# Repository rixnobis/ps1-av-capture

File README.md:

# ps1-av-capture

A capture board for the PlayStation's analog RGB and line audio. A TI TVP7002
digitises the 15 kHz RGB from the multi-out, a Cypress FX3 carries the pixels to the
host over USB 3 as a UVC camera, and a TI PCM2903C presents the audio as a USB
sound card. This first revision is one channel; the plan is three on one board
behind a hub.

Work in progress: nothing here has been built. Part availability is in
[docs/parts.md](docs/parts.md).

The video front end follows the OSSC (github.com/marqs85/ossc), which uses the
same digitiser on the same signals. The FX3 side follows Cypress application note
AN75779.

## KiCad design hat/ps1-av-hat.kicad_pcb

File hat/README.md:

# PS1 AV capture hat

One-channel PS1 capture hat for the Maker go CH32H417QEU6 dev board. Schematic: `gen_hat_sch.py`
(`tools/`); board: `tools/build_hat_pcb.py` (outline, headers, holes, placement, no routing);
`./build.sh` runs everything (ERC, netlist checks, PCB, DRC, renders in `renders/`).

## Mechanics
- The hat plugs on the dev board through two 3x19 2.54 mm headers (J4 = board U12, J5 = board U13)
  and sits 8-11 mm above it. Geometry comes from the board DXF (`tools/mg_dxf_geometry.json`,
  made by `tools/extract_mg_dxf.py`). Which DXF header is U12 is still unresolved:
  `TOP_IS_U12` in `tools/build_hat_pcb.py` (default True), flip and rebuild.
- The outline keeps 1 mm clear of the dev board's tall parts (barrel jack, screw terminal, RJ45,
  USB-A). The headers run to x = -37.5 (DXF) but the RJ45 starts at -43.1, so the outline is
  notched between two ears; the ears carry the two right-hand mounting holes.
- All four M3 holes of the dev board fall inside the hat outline (H1-H4 match them, 3.2 mm).
  Use standoffs of the header-stack height; the headers are not the only support.
- Placement is for review; nothing is routed. The dev board's tact switches and LEDs near its
  lower-left corner are covered by the hat.

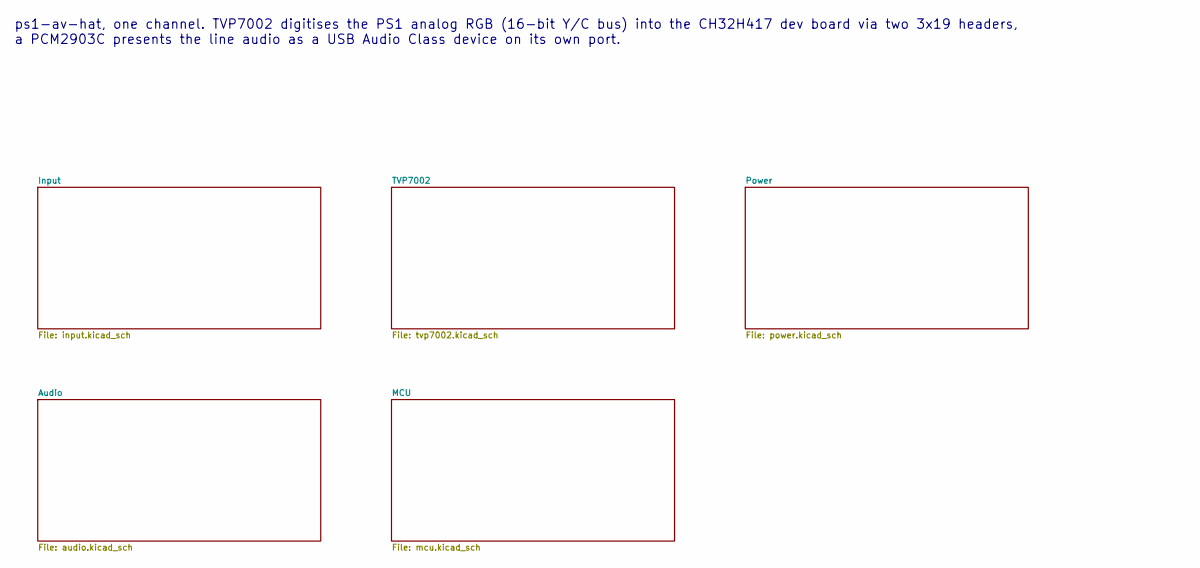
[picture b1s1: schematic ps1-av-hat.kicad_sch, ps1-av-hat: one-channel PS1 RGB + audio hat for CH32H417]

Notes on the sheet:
ps1-av-hat, one channel. TVP7002 digitises the PS1 analog RGB (16-bit Y/C bus) into the CH32H417 dev board via two 3x19 headers, a PCM2903C presents the line audio as a USB Audio Class device on its own port.

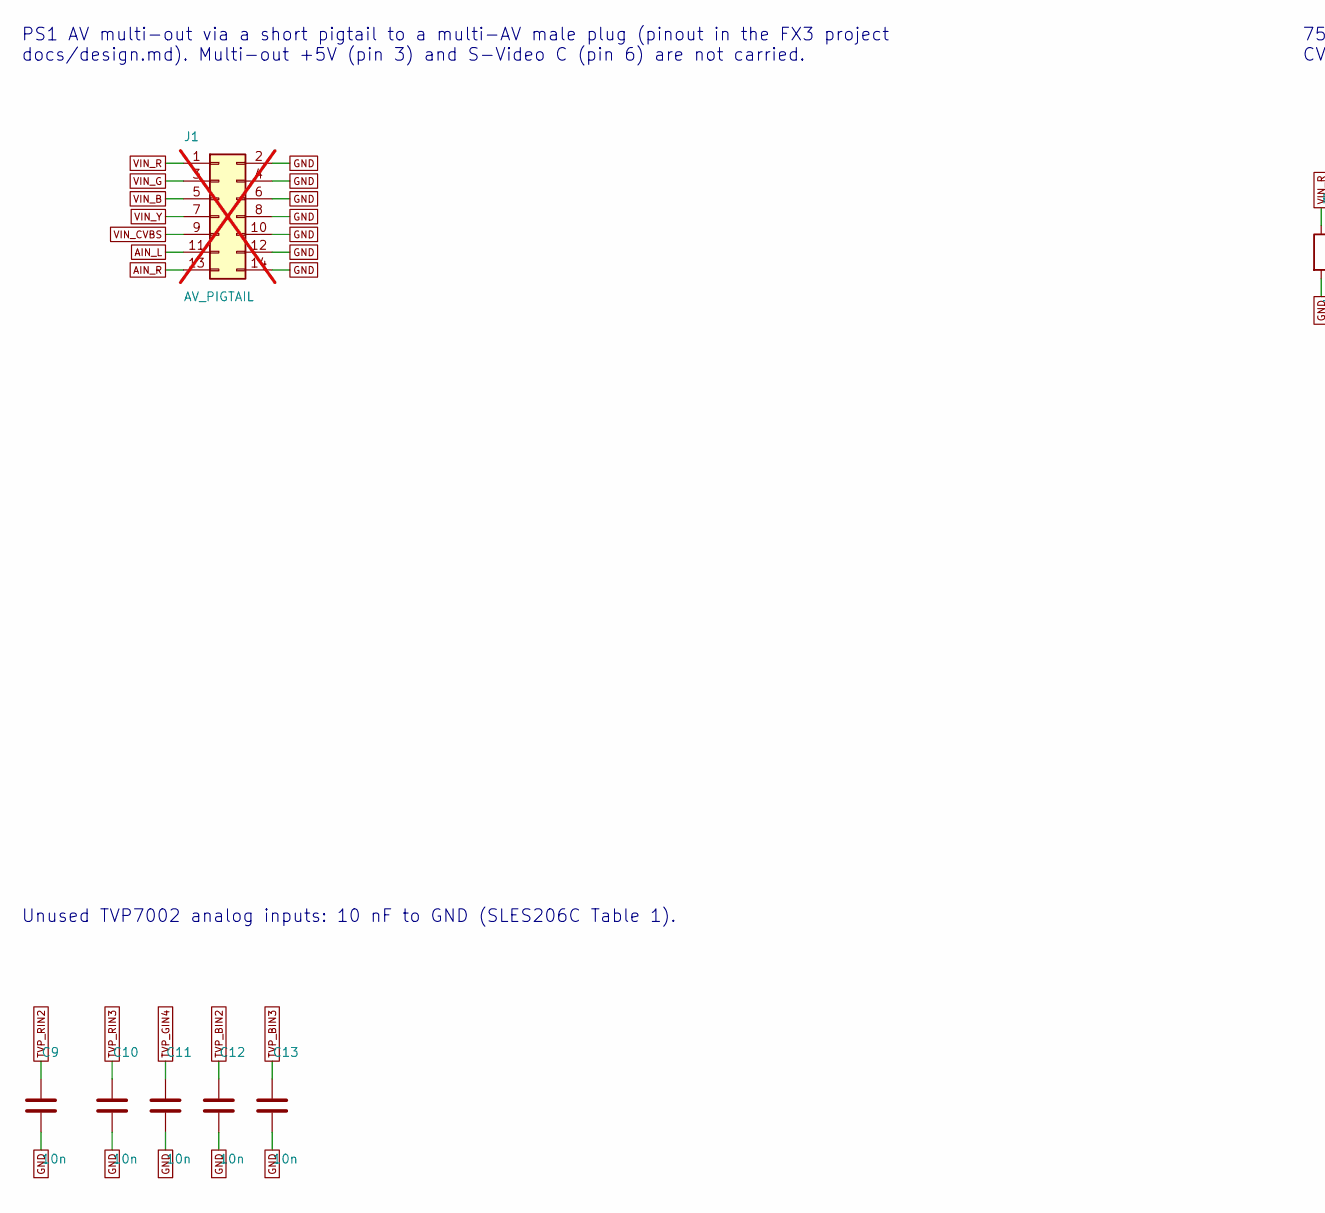
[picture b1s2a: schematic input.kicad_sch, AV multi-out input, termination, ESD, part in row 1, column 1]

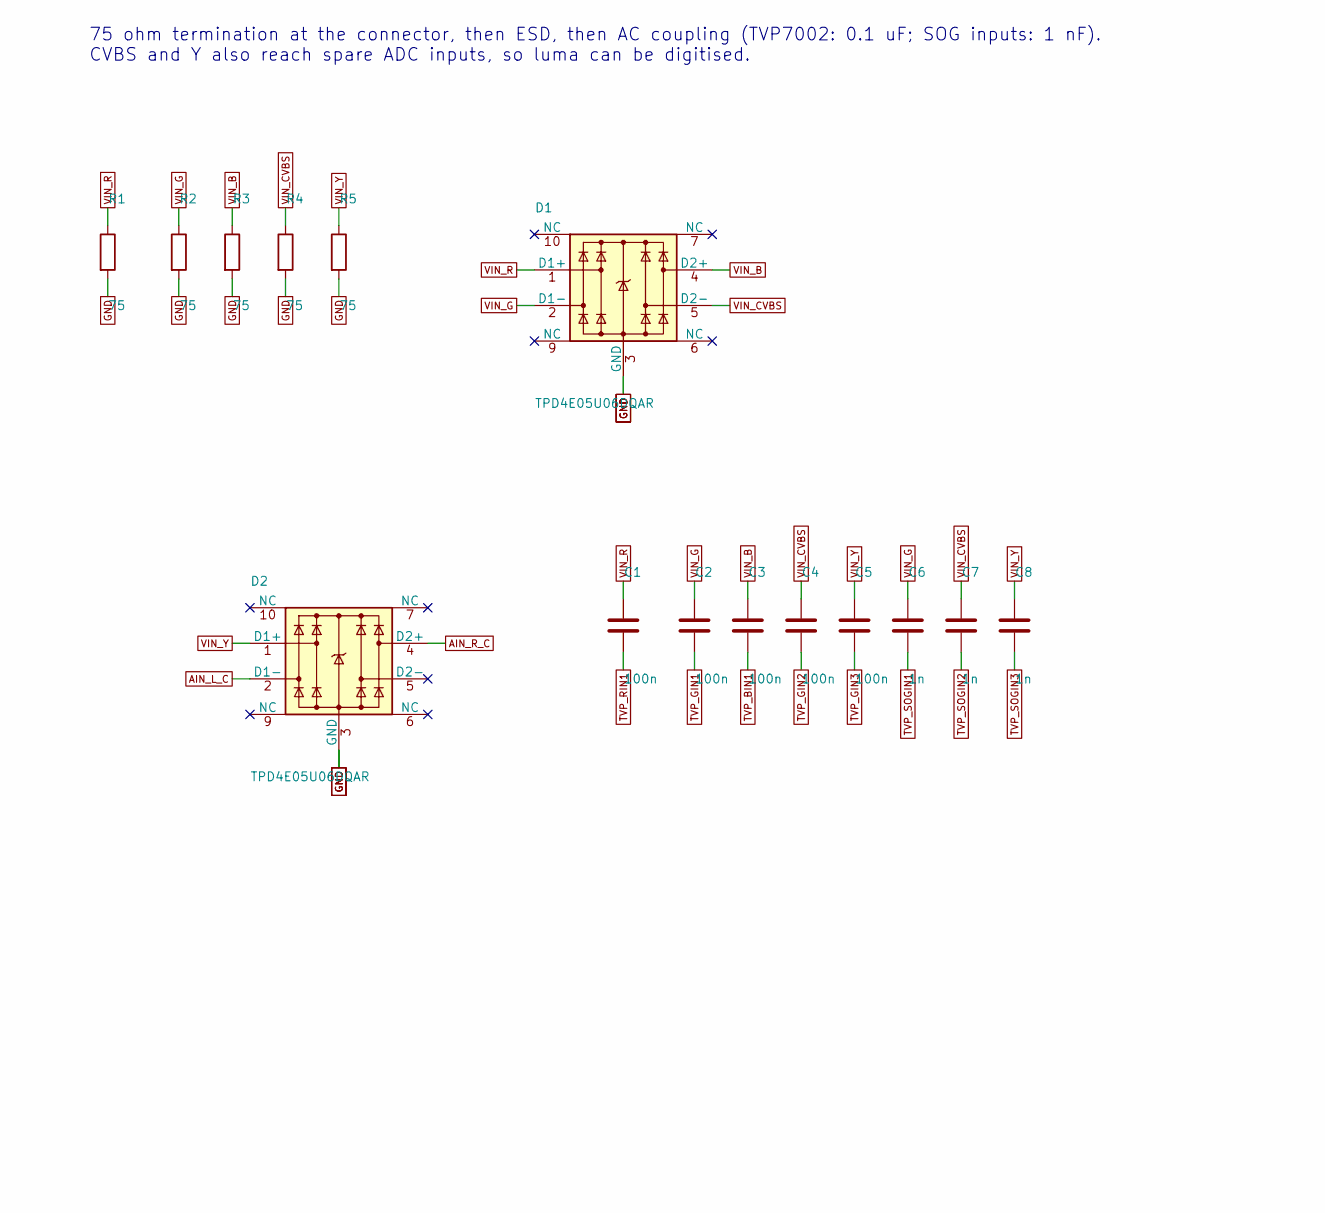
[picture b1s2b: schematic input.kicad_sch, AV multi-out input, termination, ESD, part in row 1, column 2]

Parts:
C1, C2, C3, C4, C5: 100n; C_0402_1005Metric; LCSC C1525
C6, C7, C8: 1n; C_0402_1005Metric; LCSC C1523
C9, C10, C11, C12, C13: 10n; C_0402_1005Metric; LCSC C15195
D1, D2: TPD4E05U06DQAR; USON-10_2.5x1.0mm_P0.5mm; LCSC C138714
J1: AV_PIGTAIL; JST_PHD_B14B-PHDSS_2x07_P2.00mm_Vertical; LCSC C471471; not fitted
R1, R2, R3, R4, R5: 75; R_0402_1005Metric; LCSC C25133

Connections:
AIN_L: J1.11; also elsewhere on the board
AIN_L_C: D2.2 (D1-); also elsewhere on the board
AIN_R: J1.13; also elsewhere on the board
AIN_R_C: D2.4 (D2+); also elsewhere on the board
GND: C9.2, C10.2, C11.2, C12.2, C13.2, D1.3 (GND), D1.8 (GND), D2.3 (GND), D2.8 (GND), J1.2, J1.4, J1.6, J1.8, J1.10, J1.12, J1.14, R1.2, R2.2, R3.2, R4.2, R5.2; also elsewhere on the board
TVP_BIN1: C3.2; also elsewhere on the board
TVP_BIN2: C12.1; also elsewhere on the board
TVP_BIN3: C13.1; also elsewhere on the board
TVP_GIN1: C2.2; also elsewhere on the board
TVP_GIN2: C4.2; also elsewhere on the board
TVP_GIN3: C5.2; also elsewhere on the board
TVP_GIN4: C11.1; also elsewhere on the board
TVP_RIN1: C1.2; also elsewhere on the board
TVP_RIN2: C9.1; also elsewhere on the board
TVP_RIN3: C10.1; also elsewhere on the board
TVP_SOGIN1: C6.2; also elsewhere on the board
TVP_SOGIN2: C7.2; also elsewhere on the board
TVP_SOGIN3: C8.2; also elsewhere on the board
VIN_B: C3.1, D1.4 (D2+), J1.5, R3.1
VIN_CVBS: C4.1, C7.1, D1.5 (D2-), J1.9, R4.1
VIN_G: C2.1, C6.1, D1.2 (D1-), J1.3, R2.1
VIN_R: C1.1, D1.1 (D1+), J1.1, R1.1
VIN_Y: C5.1, C8.1, D2.1 (D1+), J1.7, R5.1

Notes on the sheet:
PS1 AV multi-out via a short pigtail to a multi-AV male plug (pinout in the FX3 project docs/design.md). Multi-out +5V (pin 3) and S-Video C (pin 6) are not carried.
75 ohm termination at the connector, then ESD, then AC coupling (TVP7002: 0.1 uF; SOG inputs: 1 nF). CVBS and Y also reach spare ADC inputs, so luma can be digitised.
Unused TVP7002 analog inputs: 10 nF to GND (SLES206C Table 1).

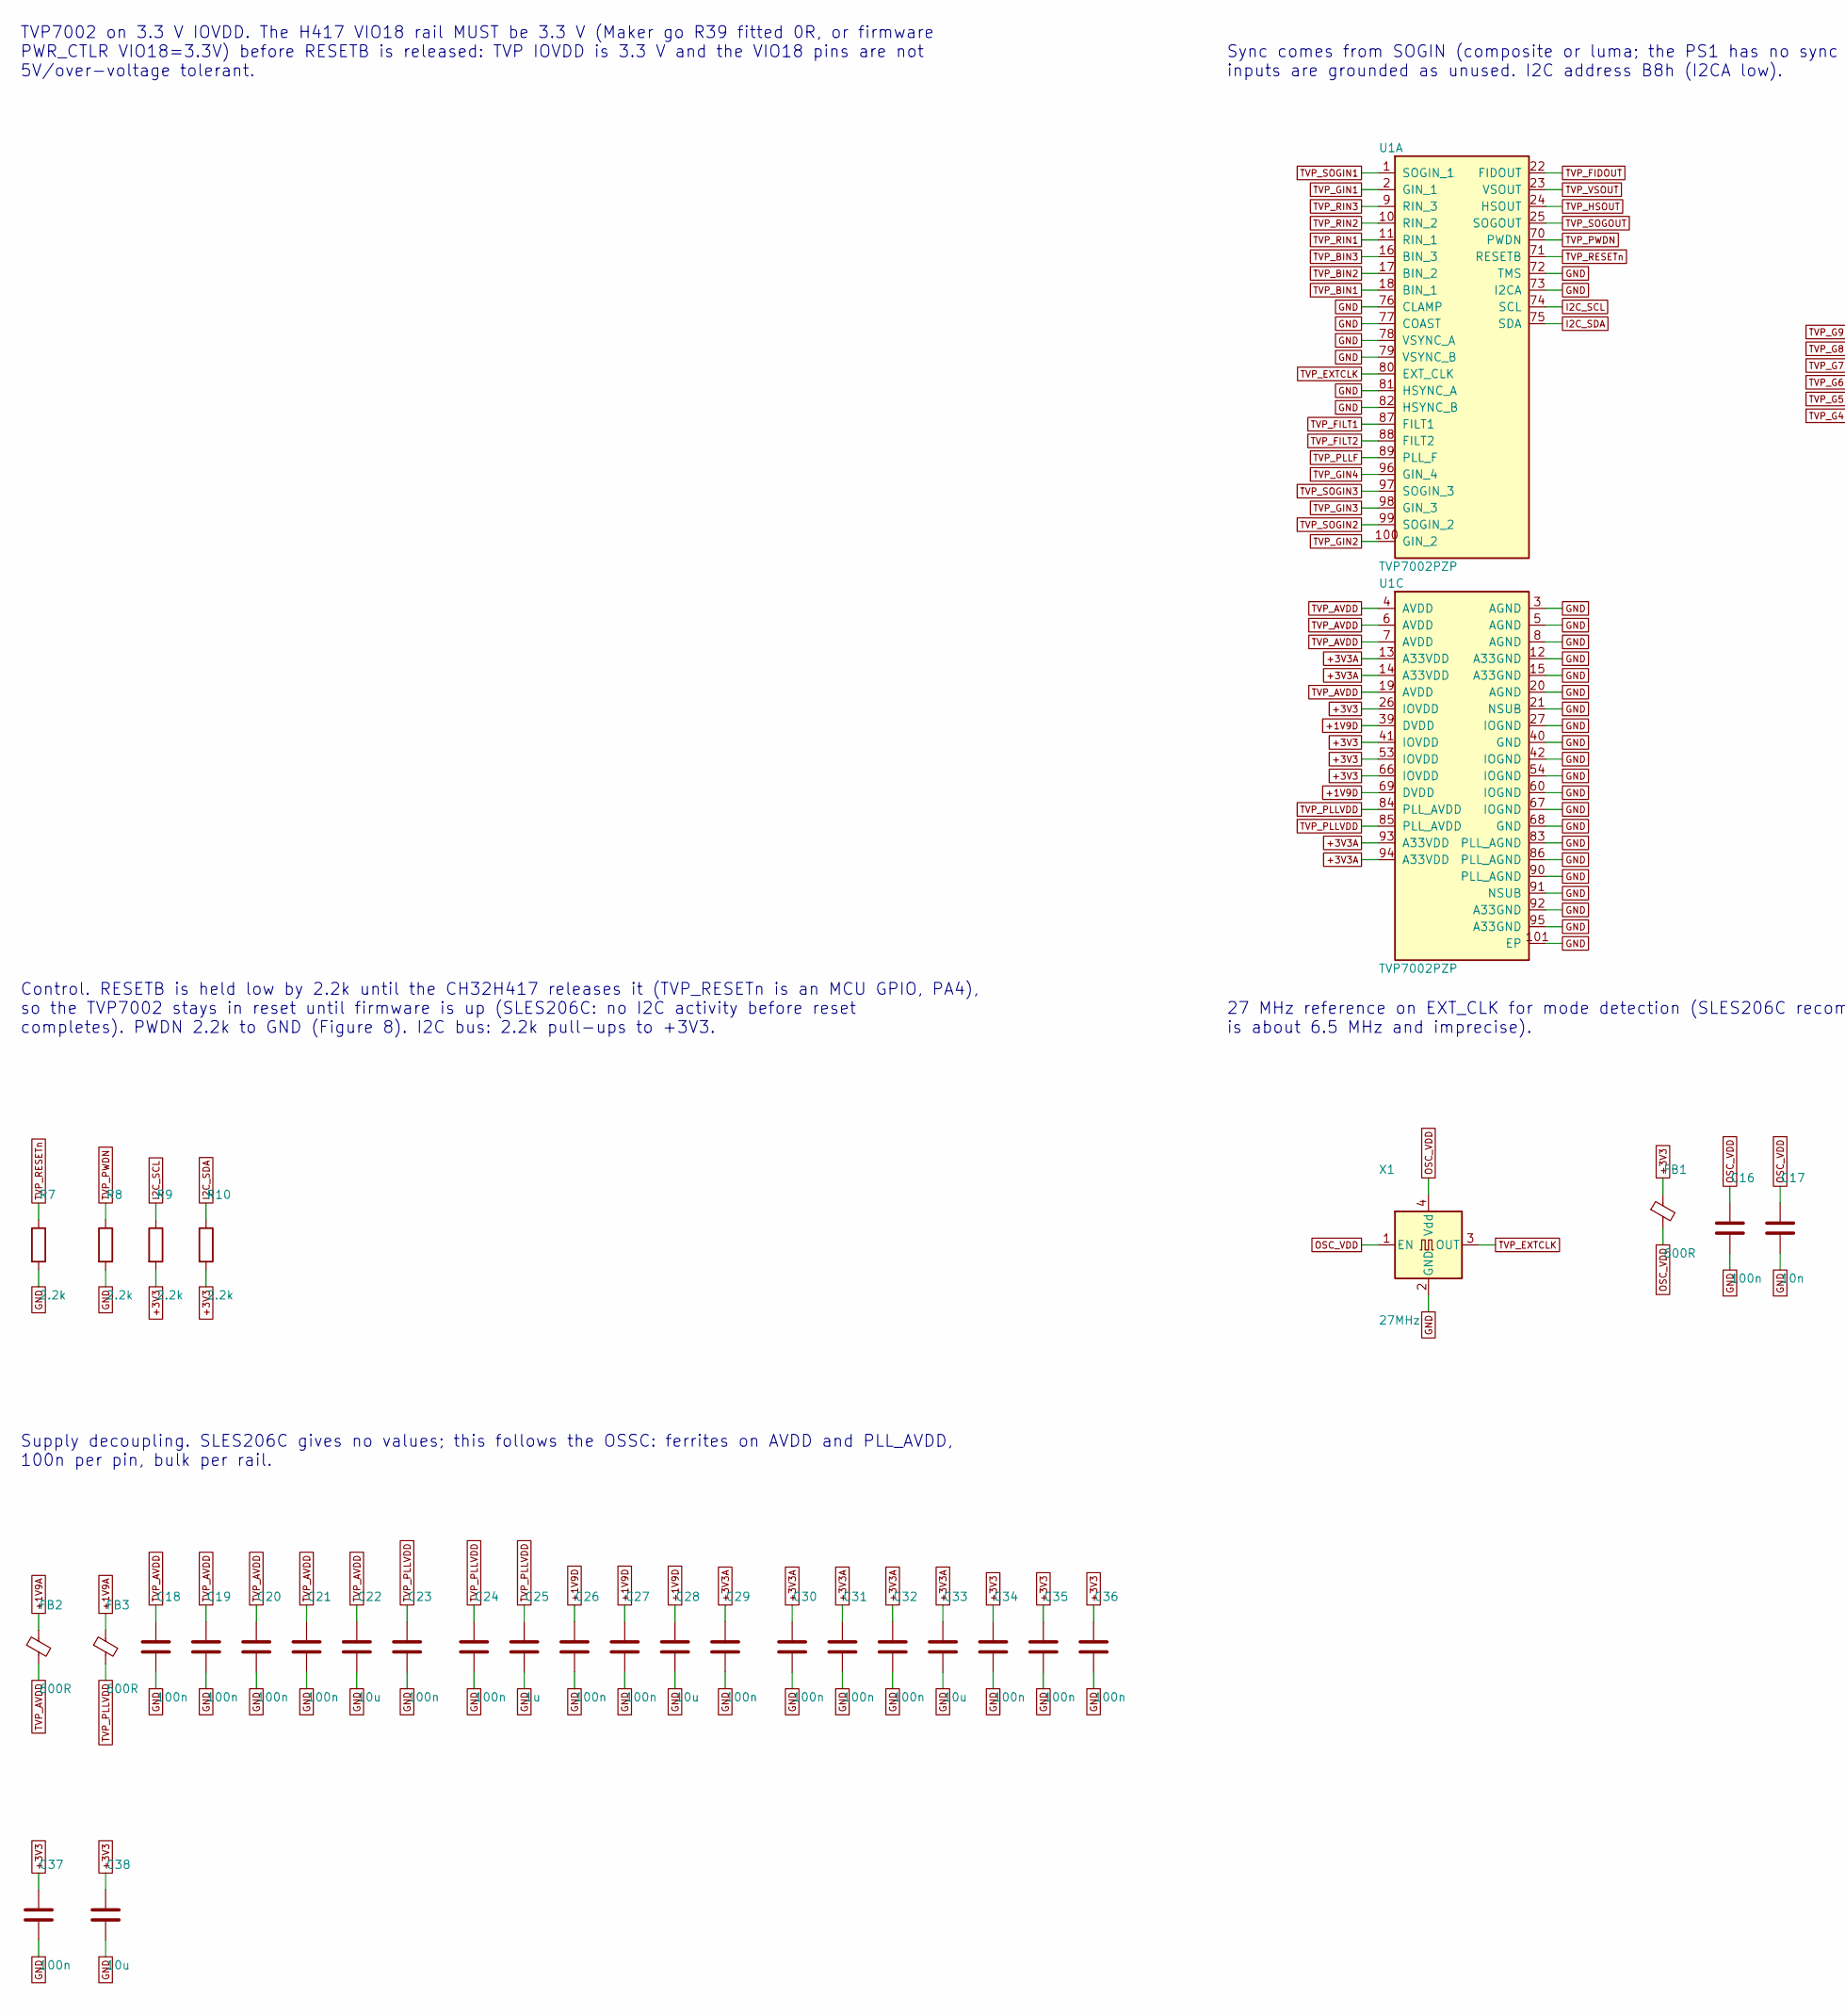
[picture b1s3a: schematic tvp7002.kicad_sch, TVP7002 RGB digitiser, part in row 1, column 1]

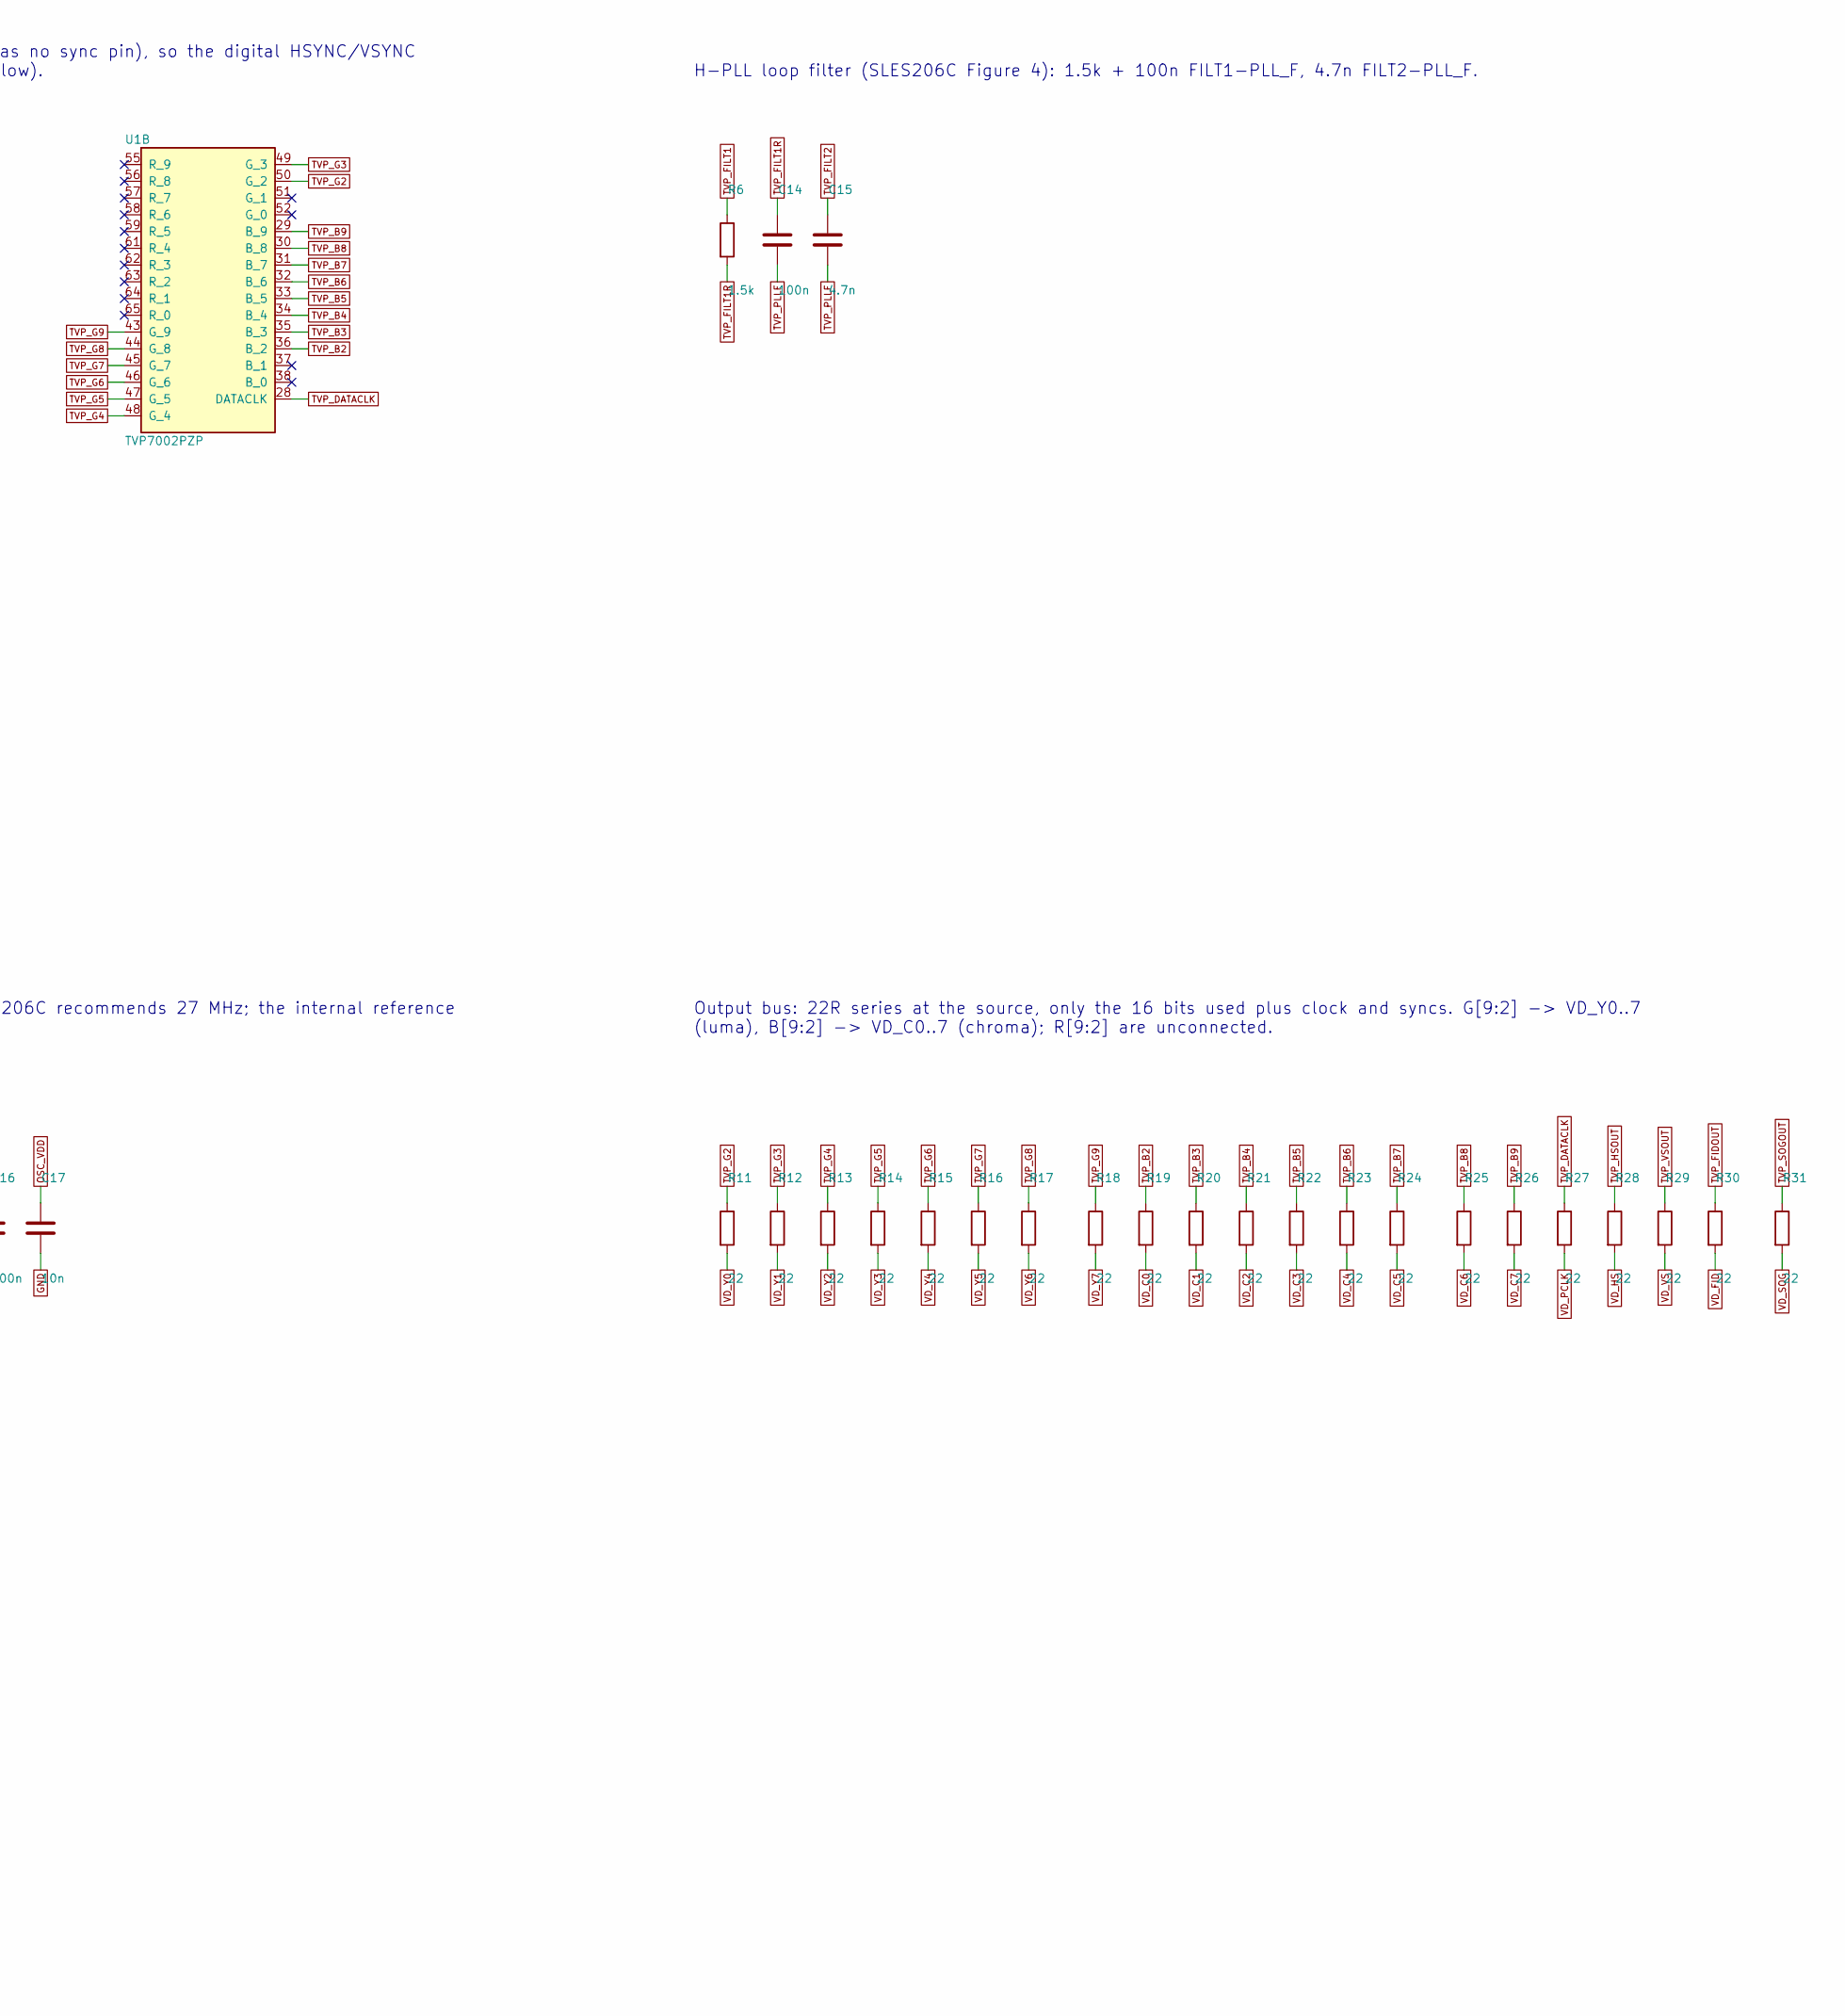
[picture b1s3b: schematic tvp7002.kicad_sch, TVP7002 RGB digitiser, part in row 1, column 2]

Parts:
C14, C16, C18, C19, C20, C21, C23, C24, C26, C27, C29, C30, C31, C32, C34, C35, C36, C37: 100n; C_0402_1005Metric; LCSC C1525
C15: 4.7n; C_0402_1005Metric; LCSC C1538
C17: 10n; C_0402_1005Metric; LCSC C15195
C22, C28, C33, C38: 10u; C_0603_1608Metric; LCSC C19702
C25: 1u; C_0402_1005Metric; LCSC C52923
FB1, FB2, FB3: 600R; L_0603_1608Metric; LCSC C108301
R6: 1.5k; R_0402_1005Metric; LCSC C25867
R7, R8, R9, R10: 2.2k; R_0402_1005Metric; LCSC C25879
R11, R12, R13, R14, R15, R16, R17, R18, R19, R20, R21, R22, R23, R24, R25, R26, R27, R28, R29, R30, R31: 22; R_0402_1005Metric; LCSC C25092
U1: TVP7002PZP; HTQFP-100_L14.0-W14.0-P0.50-LS16.0-BL-EP6.2; LCSC C3824085
X1: 27MHz; Oscillator_SMD_Abracon_ASE-4Pin_3.2x2.5mm; LCSC C725995

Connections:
+1V9A: FB2.1, FB3.1; also elsewhere on the board
+1V9D: C26.1, C27.1, C28.1, U1.39 (DVDD), U1.69 (DVDD); also elsewhere on the board
+3V3: C34.1, C35.1, C36.1, C37.1, C38.1, FB1.1, R9.2, R10.2, U1.26 (IOVDD), U1.41 (IOVDD), U1.53 (IOVDD), U1.66 (IOVDD); also elsewhere on the board
+3V3A: C29.1, C30.1, C31.1, C32.1, C33.1, U1.13 (A33VDD), U1.14 (A33VDD), U1.93 (A33VDD), U1.94 (A33VDD); also elsewhere on the board
GND: C16.2, C17.2, C18.2, C19.2, C20.2, C21.2, C22.2, C23.2, C24.2, C25.2, C26.2, C27.2, C28.2, C29.2, C30.2, C31.2, C32.2, C33.2, C34.2, C35.2, C36.2, C37.2, C38.2, R7.2, R8.2, U1.3 (AGND), U1.5 (AGND), U1.8 (AGND), U1.12 (A33GND), U1.15 (A33GND), U1.20 (AGND), U1.21 (NSUB), U1.27 (IOGND), U1.40 (GND), U1.42 (IOGND), U1.54 (IOGND), U1.60 (IOGND), U1.67 (IOGND), U1.68 (GND), U1.72 (TMS), U1.73 (I2CA), U1.76 (CLAMP), U1.77 (COAST), U1.78 (VSYNC_A), U1.79 (VSYNC_B), U1.81 (HSYNC_A), U1.82 (HSYNC_B), U1.83 (PLL_AGND), U1.86 (PLL_AGND), U1.90 (PLL_AGND), U1.91 (NSUB), U1.92 (A33GND), U1.95 (A33GND), U1.101 (EP), X1.2 (GND); also elsewhere on the board
I2C_SCL: R9.1, U1.74 (SCL); also elsewhere on the board
I2C_SDA: R10.1, U1.75 (SDA); also elsewhere on the board
OSC_VDD: C16.1, C17.1, FB1.2, X1.1 (EN), X1.4 (Vdd)
TVP_AVDD: C18.1, C19.1, C20.1, C21.1, C22.1, FB2.2, U1.4 (AVDD), U1.6 (AVDD), U1.7 (AVDD), U1.19 (AVDD)
TVP_B2: R19.1, U1.36 (B_2)
TVP_B3: R20.1, U1.35 (B_3)
TVP_B4: R21.1, U1.34 (B_4)
TVP_B5: R22.1, U1.33 (B_5)
TVP_B6: R23.1, U1.32 (B_6)
TVP_B7: R24.1, U1.31 (B_7)
TVP_B8: R25.1, U1.30 (B_8)
TVP_B9: R26.1, U1.29 (B_9)
TVP_BIN1: U1.18 (BIN_1); also elsewhere on the board
TVP_BIN2: U1.17 (BIN_2); also elsewhere on the board
TVP_BIN3: U1.16 (BIN_3); also elsewhere on the board
TVP_DATACLK: R27.1, U1.28 (DATACLK)
TVP_EXTCLK: U1.80 (EXT_CLK), X1.3 (OUT)
TVP_FIDOUT: R30.1, U1.22 (FIDOUT)
TVP_FILT1: R6.1, U1.87 (FILT1)
TVP_FILT1R: C14.1, R6.2
TVP_FILT2: C15.1, U1.88 (FILT2)
TVP_G2: R11.1, U1.50 (G_2)
TVP_G3: R12.1, U1.49 (G_3)
TVP_G4: R13.1, U1.48 (G_4)
TVP_G5: R14.1, U1.47 (G_5)
TVP_G6: R15.1, U1.46 (G_6)
TVP_G7: R16.1, U1.45 (G_7)
TVP_G8: R17.1, U1.44 (G_8)
TVP_G9: R18.1, U1.43 (G_9)
TVP_GIN1: U1.2 (GIN_1); also elsewhere on the board
TVP_GIN2: U1.100 (GIN_2); also elsewhere on the board
TVP_GIN3: U1.98 (GIN_3); also elsewhere on the board
TVP_GIN4: U1.96 (GIN_4); also elsewhere on the board
TVP_HSOUT: R28.1, U1.24 (HSOUT)
TVP_PLLF: C14.2, C15.2, U1.89 (PLL_F)
TVP_PLLVDD: C23.1, C24.1, C25.1, FB3.2, U1.84 (PLL_AVDD), U1.85 (PLL_AVDD)
TVP_PWDN: R8.1, U1.70 (PWDN)
TVP_RESETn: R7.1, U1.71 (RESETB); also elsewhere on the board
TVP_RIN1: U1.11 (RIN_1); also elsewhere on the board
TVP_RIN2: U1.10 (RIN_2); also elsewhere on the board
TVP_RIN3: U1.9 (RIN_3); also elsewhere on the board
TVP_SOGIN1: U1.1 (SOGIN_1); also elsewhere on the board
TVP_SOGIN2: U1.99 (SOGIN_2); also elsewhere on the board
TVP_SOGIN3: U1.97 (SOGIN_3); also elsewhere on the board
TVP_SOGOUT: R31.1, U1.25 (SOGOUT)
TVP_VSOUT: R29.1, U1.23 (VSOUT)
VD_C0: R19.2; also elsewhere on the board
VD_C1: R20.2; also elsewhere on the board
VD_C2: R21.2; also elsewhere on the board
VD_C3: R22.2; also elsewhere on the board
VD_C4: R23.2; also elsewhere on the board
VD_C5: R24.2; also elsewhere on the board
VD_C6: R25.2; also elsewhere on the board
VD_C7: R26.2; also elsewhere on the board
VD_FID: R30.2; also elsewhere on the board
VD_HS: R28.2; also elsewhere on the board
VD_PCLK: R27.2; also elsewhere on the board
VD_SOG: R31.2; also elsewhere on the board
VD_VS: R29.2; also elsewhere on the board
VD_Y0: R11.2; also elsewhere on the board
VD_Y1: R12.2; also elsewhere on the board
VD_Y2: R13.2; also elsewhere on the board
VD_Y3: R14.2; also elsewhere on the board
VD_Y4: R15.2; also elsewhere on the board
VD_Y5: R16.2; also elsewhere on the board
VD_Y6: R17.2; also elsewhere on the board
VD_Y7: R18.2; also elsewhere on the board

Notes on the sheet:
TVP7002 on 3.3 V IOVDD. The H417 VIO18 rail MUST be 3.3 V (Maker go R39 fitted 0R, or firmware PWR_CTLR VIO18=3.3V) before RESETB is released: TVP IOVDD is 3.3 V and the VIO18 pins are not 5V/over-voltage tolerant.
Sync comes from SOGIN (composite or luma; the PS1 has no sync pin), so the digital HSYNC/VSYNC inputs are grounded as unused. I2C address B8h (I2CA low).
H-PLL loop filter (SLES206C Figure 4): 1.5k + 100n FILT1-PLL_F, 4.7n FILT2-PLL_F.
Control. RESETB is held low by 2.2k until the CH32H417 releases it (TVP_RESETn is an MCU GPIO, PA4), so the TVP7002 stays in reset until firmware is up (SLES206C: no I2C activity before reset completes). PWDN 2.2k to GND (Figure 8). I2C bus: 2.2k pull-ups to +3V3.
27 MHz reference on EXT_CLK for mode detection (SLES206C recommends 27 MHz; the internal reference is about 6.5 MHz and imprecise).
Output bus: 22R series at the source, only the 16 bits used plus clock and syncs. G[9:2] -> VD_Y0..7 (luma), B[9:2] -> VD_C0..7 (chroma); R[9:2] are unconnected.
Supply decoupling. SLES206C gives no values; this follows the OSSC: ferrites on AVDD and PLL_AVDD, 100n per pin, bulk per rail.

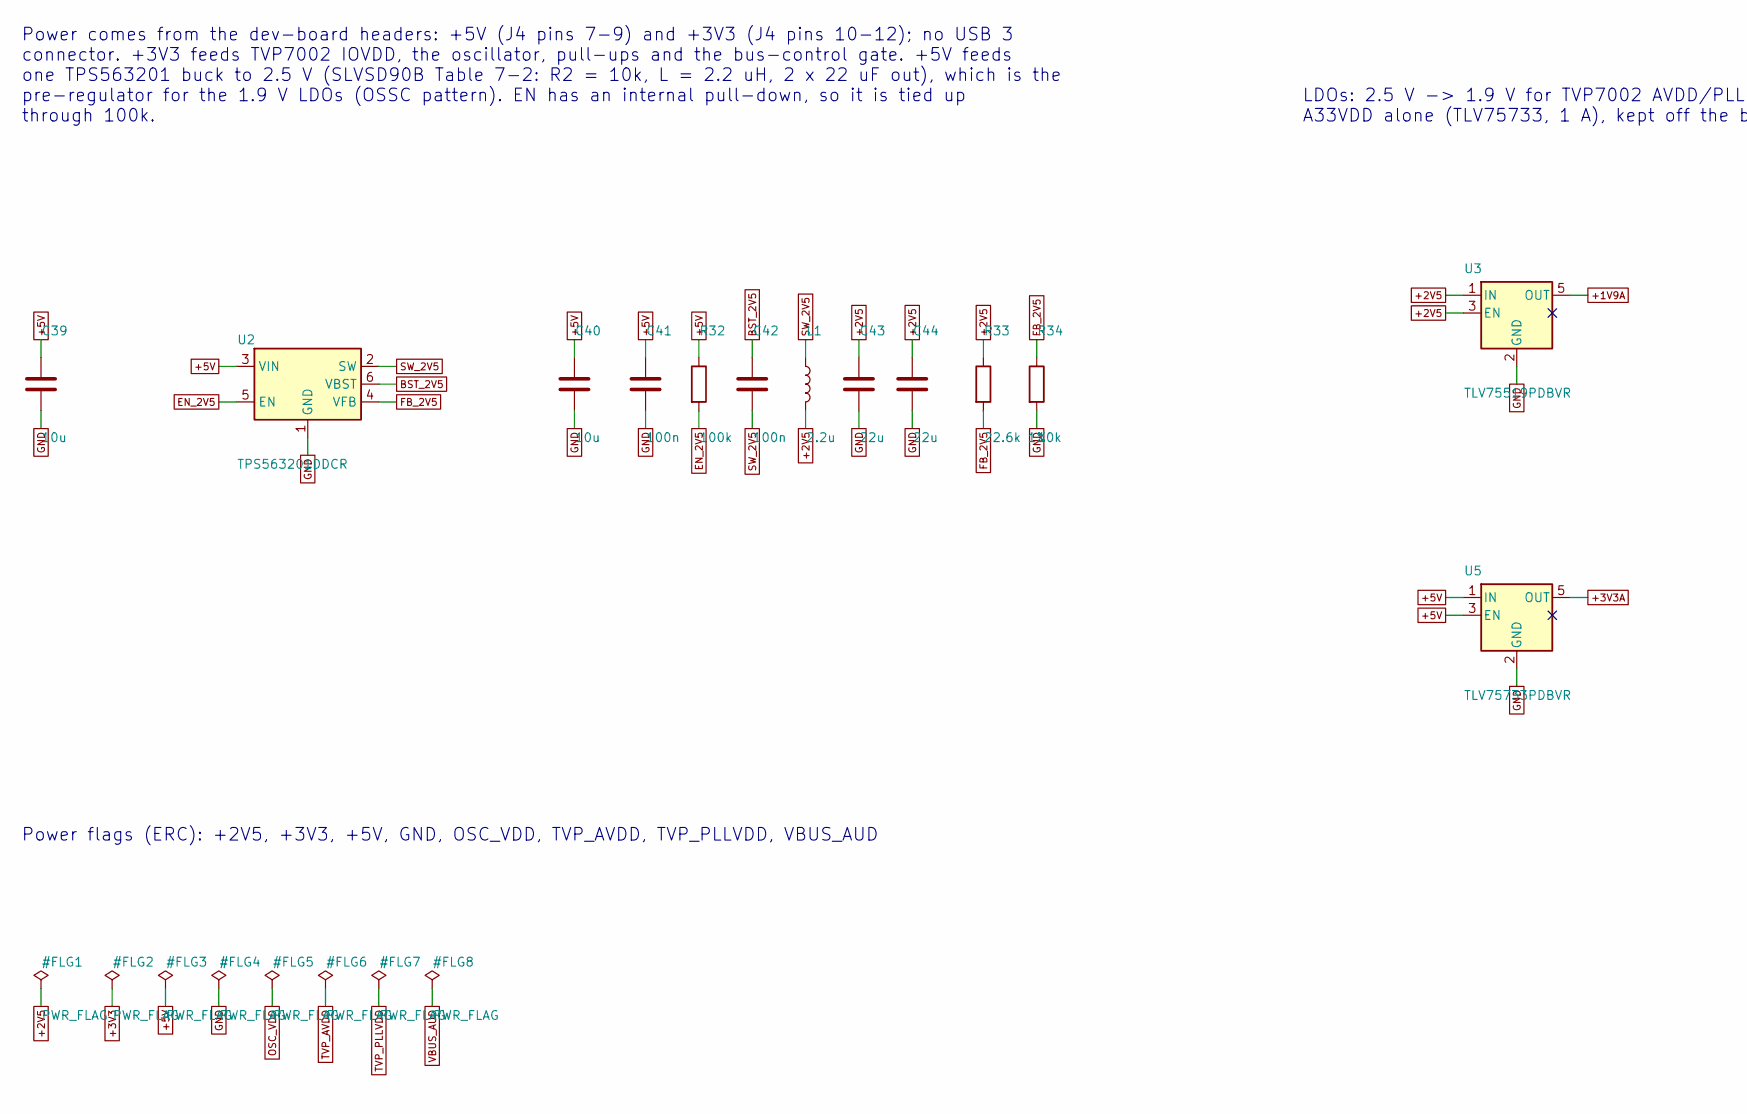
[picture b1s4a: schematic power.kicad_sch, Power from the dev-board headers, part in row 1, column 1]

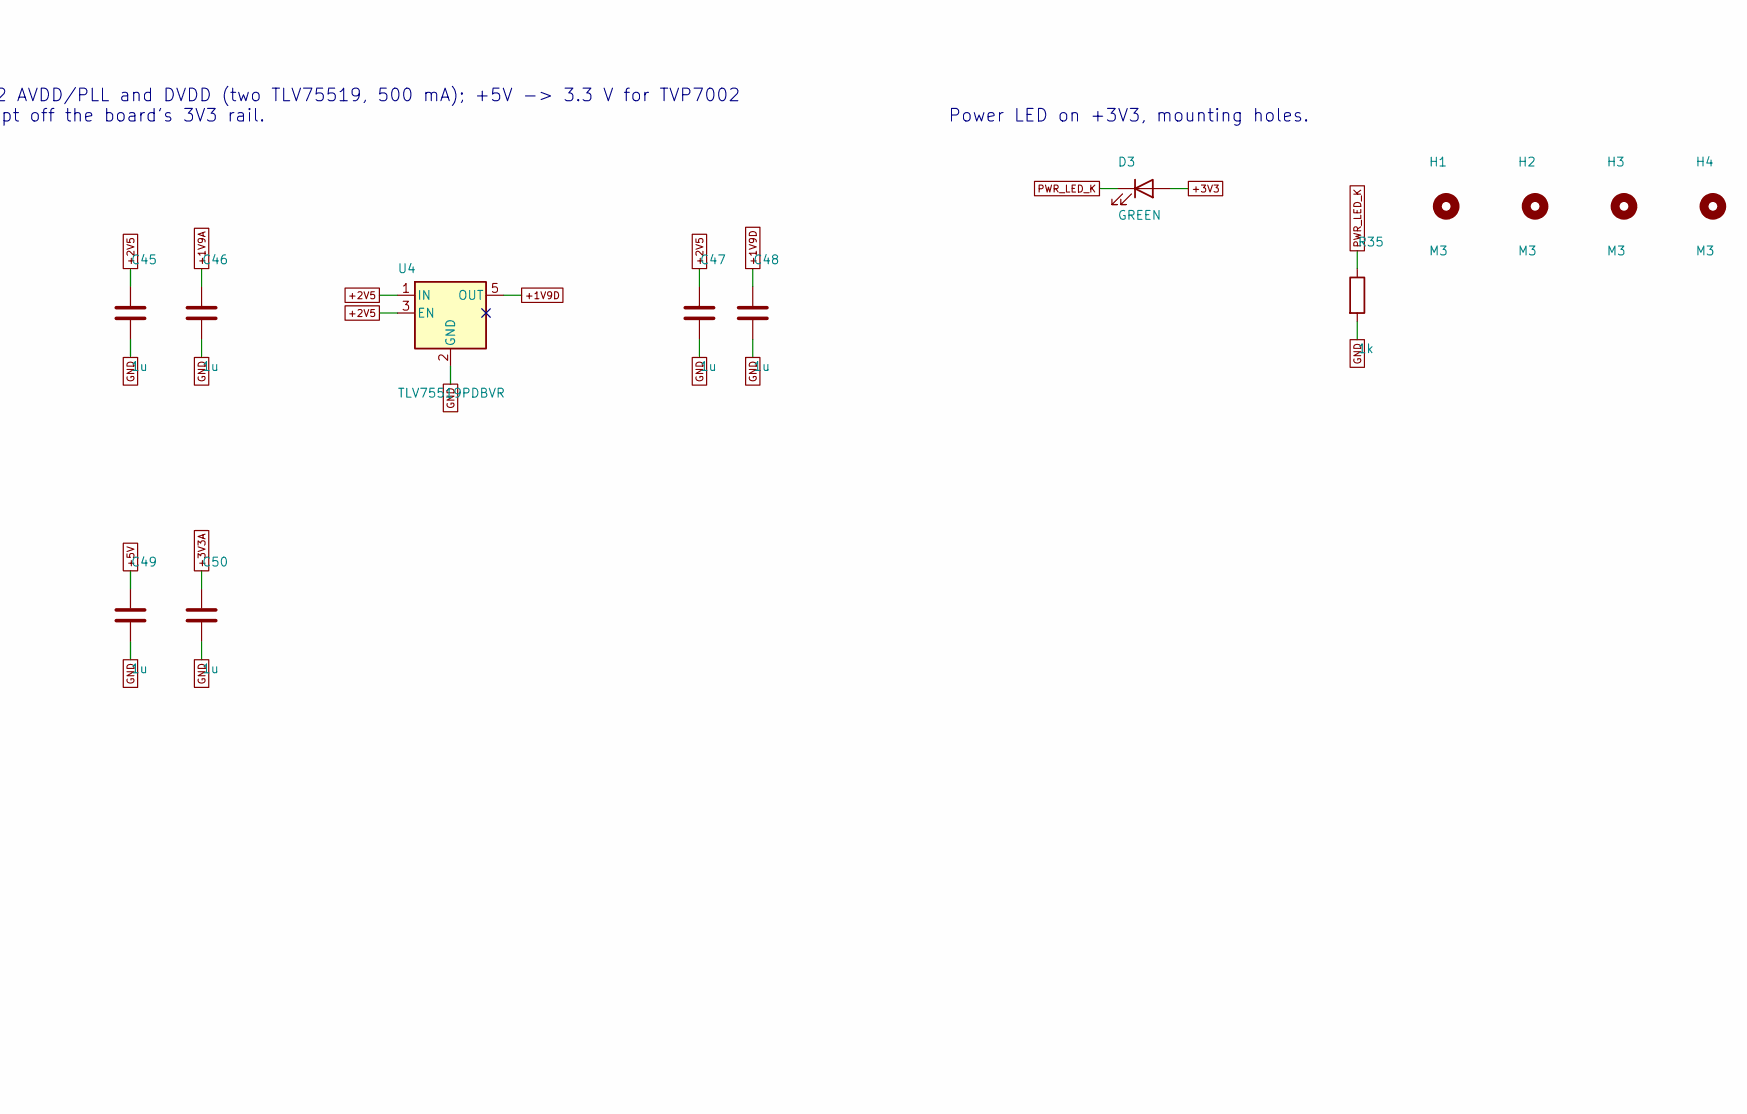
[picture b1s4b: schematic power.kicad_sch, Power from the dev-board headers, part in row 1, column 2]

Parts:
C39, C40: 10u; C_0603_1608Metric; LCSC C19702
C41, C42: 100n; C_0402_1005Metric; LCSC C1525
C43, C44: 22u; C_0805_2012Metric; LCSC C45783
C45, C46, C47, C48, C49, C50: 1u; C_0402_1005Metric; LCSC C52923
D3: GREEN; LED_0603_1608Metric; LCSC C2986059
H1, H2, H3, H4: M3; MountingHole_3.2mm_M3
L1: 2.2u; L_Sunlord_SWPA4030S; LCSC C36409
R32: 100k; R_0402_1005Metric; LCSC C25741
R33: 22.6k 1%; R_0402_1005Metric; LCSC C26960
R34: 10k; R_0402_1005Metric; LCSC C25744
R35: 1k; R_0402_1005Metric; LCSC C11702
U2: TPS563201DDCR; SOT-23-6_L2.9-W1.6-P0.95-LS2.8-BR; LCSC C116592
U3, U4: TLV75519PDBVR; SOT-23-5; LCSC C2865381
U5: TLV75733PDBVR; SOT-23-5; LCSC C485517

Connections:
+1V9A: C46.1, U3.5 (OUT); also elsewhere on the board
+1V9D: C48.1, U4.5 (OUT); also elsewhere on the board
+2V5: C43.1, C44.1, C45.1, C47.1, L1.2, R33.1, U3.1 (IN), U3.3 (EN), U4.1 (IN), U4.3 (EN)
+3V3: D3.2 (A); also elsewhere on the board
+3V3A: C50.1, U5.5 (OUT); also elsewhere on the board
+5V: C39.1, C40.1, C41.1, C49.1, R32.1, U2.3 (VIN), U5.1 (IN), U5.3 (EN); also elsewhere on the board
BST_2V5: C42.1, U2.6 (VBST)
EN_2V5: R32.2, U2.5 (EN)
FB_2V5: R33.2, R34.1, U2.4 (VFB)
GND: C39.2, C40.2, C41.2, C43.2, C44.2, C45.2, C46.2, C47.2, C48.2, C49.2, C50.2, R34.2, R35.2, U2.1 (GND), U3.2 (GND), U4.2 (GND), U5.2 (GND); also elsewhere on the board
PWR_LED_K: D3.1 (K), R35.1
SW_2V5: C42.2, L1.1, U2.2 (SW)

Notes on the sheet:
Power comes from the dev-board headers: +5V (J4 pins 7-9) and +3V3 (J4 pins 10-12); no USB 3 connector. +3V3 feeds TVP7002 IOVDD, the oscillator, pull-ups and the bus-control gate. +5V feeds one TPS563201 buck to 2.5 V (SLVSD90B Table 7-2: R2 = 10k, L = 2.2 uH, 2 x 22 uF out), which is the pre-regu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
LDOs: 2.5 V -> 1.9 V for TVP7002 AVDD/PLL and DVDD (two TLV75519, 500 mA); +5V -> 3.3 V for TVP7002 A33VDD alone (TLV75733, 1 A), kept off the board's 3V3 rail.
Power LED on +3V3, mounting holes.
Power flags (ERC): +2V5, +3V3, +5V, GND, OSC_VDD, TVP_AVDD, TVP_PLLVDD, VBUS_AUD
